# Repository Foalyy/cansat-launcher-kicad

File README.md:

Main electronics board (Kicad project) for the Argon CanSat launchers : https://github.com/Foalyy/cansat-launcher

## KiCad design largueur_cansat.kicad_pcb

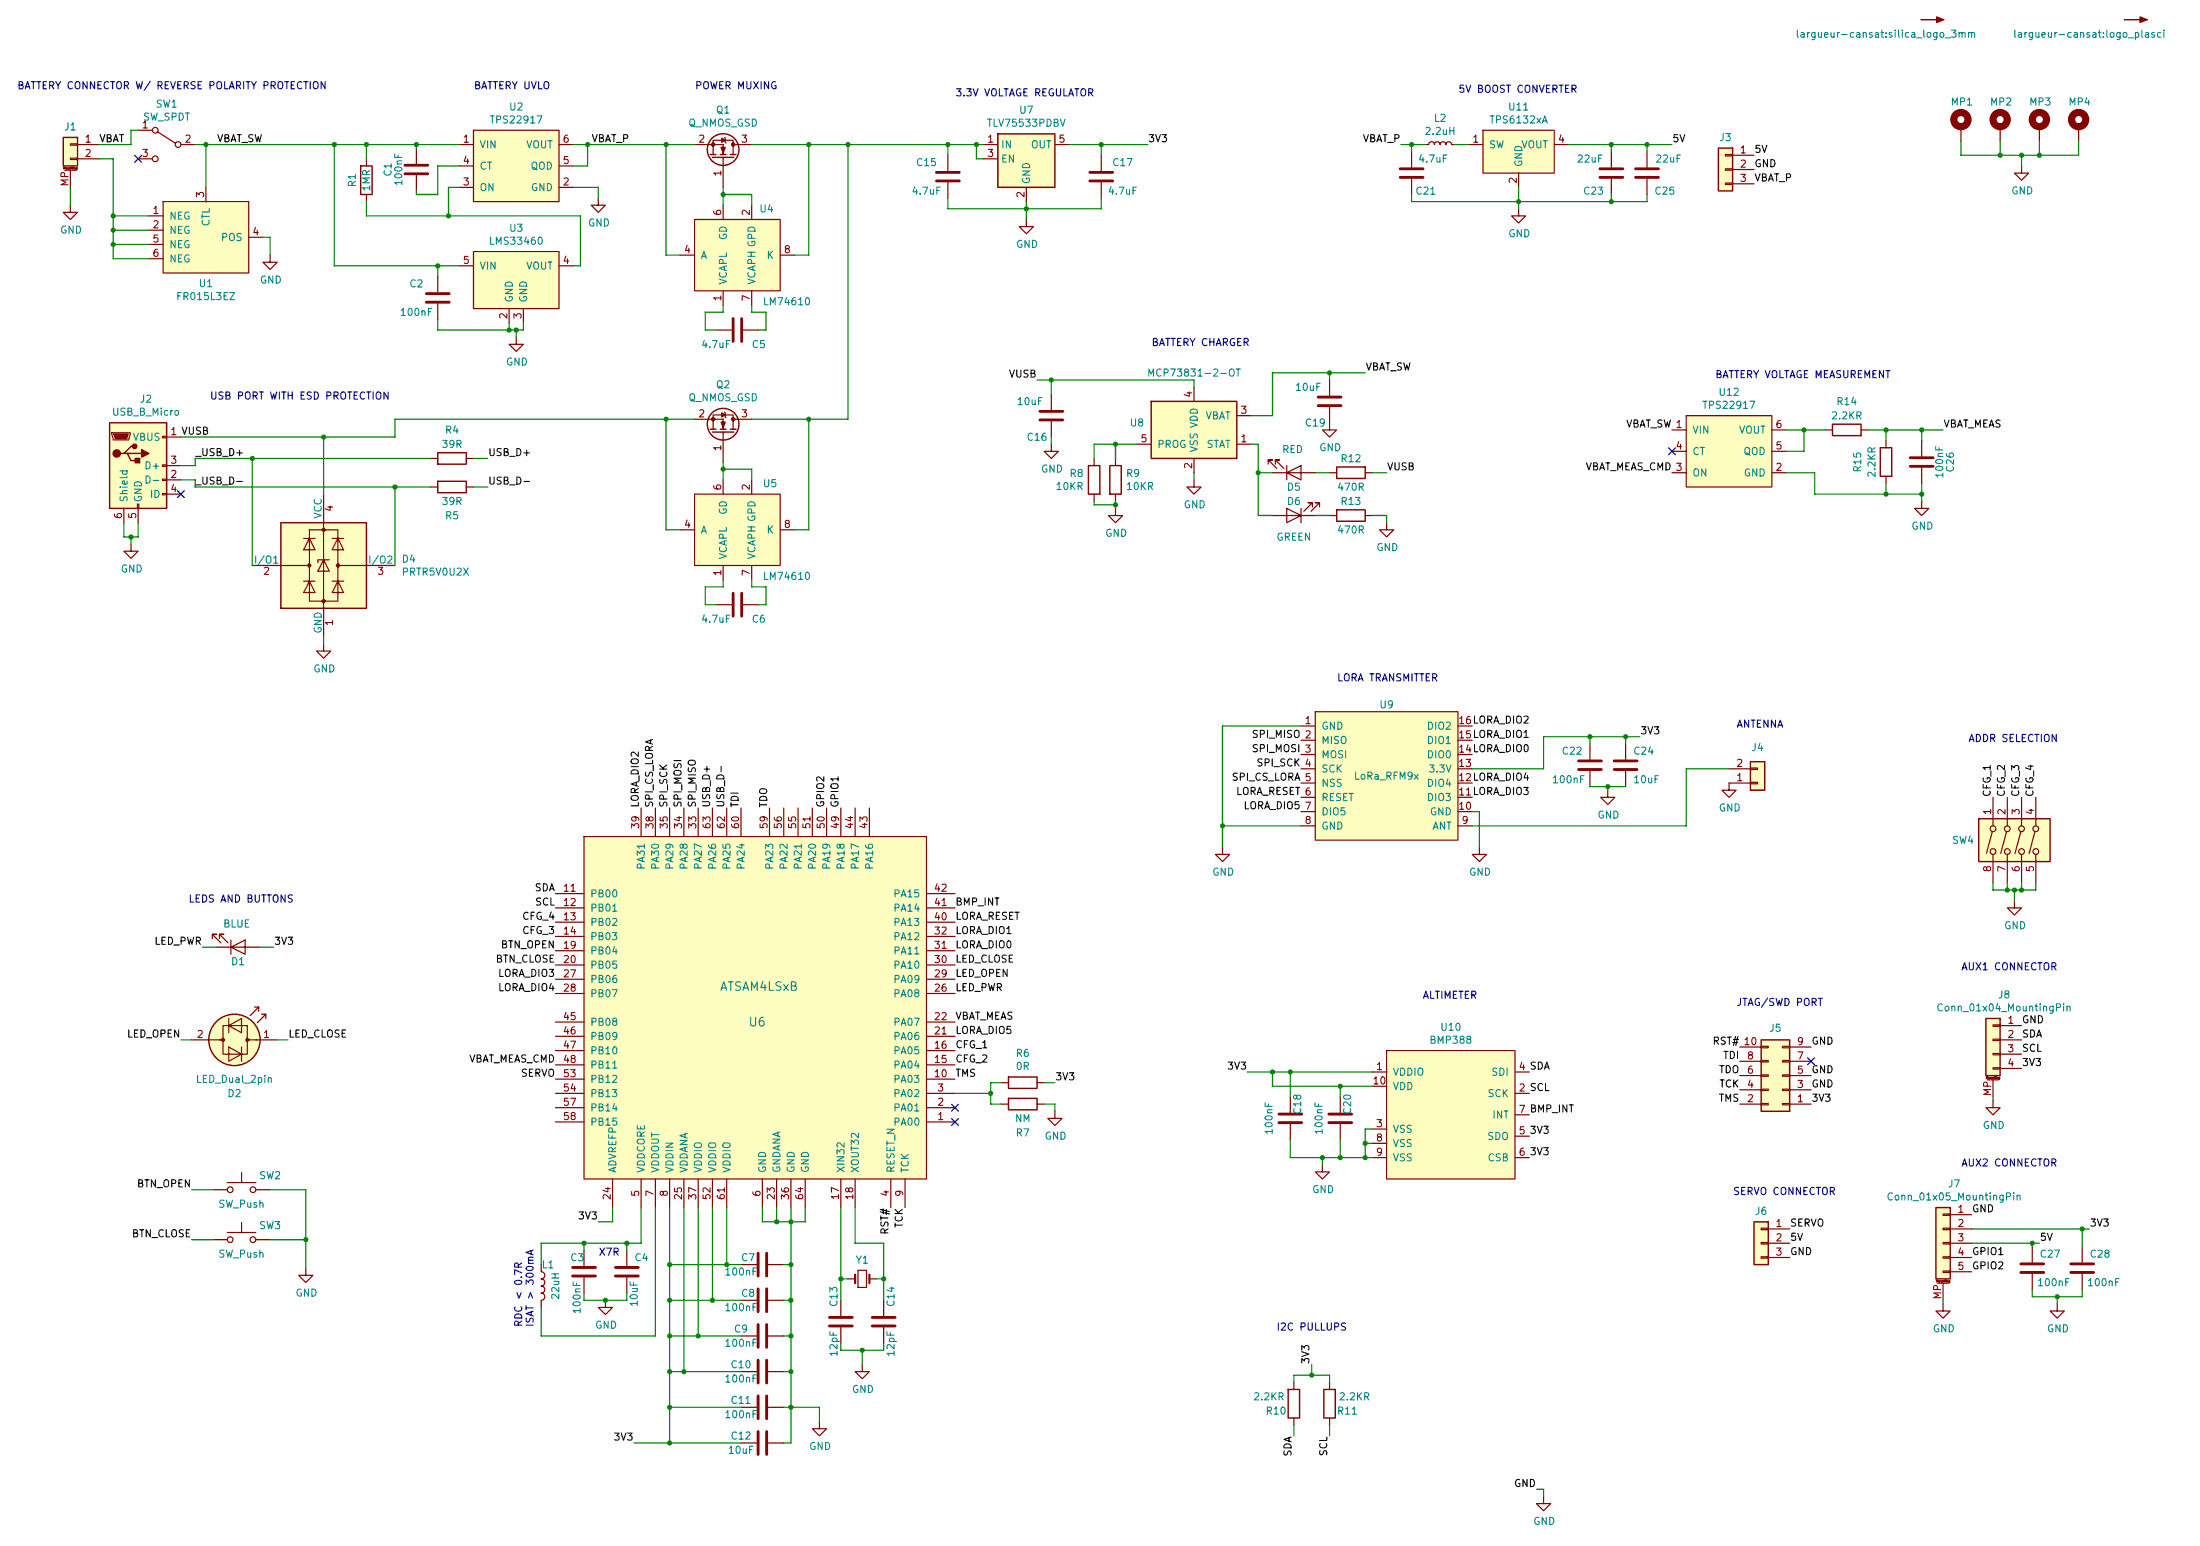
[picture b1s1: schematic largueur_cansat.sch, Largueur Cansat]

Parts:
C1, C2, C3, C7, C8, C9, C10, C11, C18, C20, C22, C26, C27, C28: 100nF; C_0603_1608Metric_Pad1.05x0.95mm_HandSolder; mpn 885012206071
C4, C12, C16, C19, C24: 10uF; C_0603_1608Metric_Pad1.05x0.95mm_HandSolder; mpn GRM188R61A106KE69J
C5, C6, C15, C17, C21: 4.7uF; C_0603_1608Metric_Pad1.05x0.95mm_HandSolder; mpn CC0603MRX5R6BB475
C13, C14: 12pF; C_0603_1608Metric_Pad1.05x0.95mm_HandSolder; mpn C0603C120K5RACTU
C23, C25: 22uF; C_0603_1608Metric_Pad1.05x0.95mm_HandSolder; mpn C1608X5R1A226M080AC
D1: BLUE; SSF-LXH103; mpn SSF-LXH103USBD
D2: LED_Dual_2pin; SSF-LXH103; mpn SSF-LXH103HGW
D4: PRTR5V0U2X; SOT-143; mpn PRTR5V0U2X
D5: RED; LED_Rectangular_W3.9mm_H1.9mm; mpn WP144SRDT
D6: GREEN; LED_Rectangular_W3.9mm_H1.9mm; mpn WP144GDT
J1: Conn_01x02_MountingPin; JST_SH_SM02B-SRSS-TB_1x02-1MP_P1.00mm_Horizontal
J2: USB_B_Micro; USB_Micro-B_Molex-105017-0001; mpn 105017-0001
J3: Conn_01x03; PinHeader_1x03_P2.54mm_Vertical
J4: Conn_01x02; antenna_sma_ufl
J5: Conn_02x05_Odd_Even; jtag_connector
J6: Conn_01x03; PinHeader_1x03_P2.54mm_Horizontal
J7: Conn_01x05_MountingPin; JST_SH_SM05B-SRSS-TB_1x05-1MP_P1.00mm_Horizontal
J8: Conn_01x04_MountingPin; JST_SH_SM04B-SRSS-TB_1x04-1MP_P1.00mm_Horizontal
L1: 22uH; L_1210_3225Metric_Pad1.42x2.65mm_HandSolder; mpn CBC3225T220MRV
L2: 2.2uH; L_0805_2012Metric; mpn TFM201610GHM-2R2MTAA
MP1, MP2, MP3, MP4: MountingHole_Pad; MountingHole_2.7mm_M2.5_Pad
Q1, Q2: Q_NMOS_GSD; SOT-23; mpn NTR3C21NZT1G
R1: 1MR; R_0603_1608Metric_Pad1.05x0.95mm_HandSolder
R4, R5: 39R; R_0603_1608Metric_Pad1.05x0.95mm_HandSolder; mpn RC0603FR-0739RL
R6: 0R; R_0603_1608Metric_Pad1.05x0.95mm_HandSolder; mpn AC0603JR-130RL
R7: NM; R_0603_1608Metric_Pad1.05x0.95mm_HandSolder
R8, R9: 10KR; R_0603_1608Metric_Pad1.05x0.95mm_HandSolder; mpn RC0603FR-0710KL
R10, R11, R14, R15: 2.2KR; R_0603_1608Metric_Pad1.05x0.95mm_HandSolder; mpn RC0603JR-072K2L
R12, R13: 470R; R_0603_1608Metric_Pad1.05x0.95mm_HandSolder; mpn RC0603FR-07470RL
SW1: SW_SPDT; SSSS213100; mpn SSSS213100
SW2: SW_Push; SW_Tactile_SPST_Angled_PTS645Vx83-2LFS; mpn 1-1825027-2
SW3: SW_Push; SW_Tactile_SPST_Angled_PTS645Vx83-2LFS; mpn FSMRA4JH04
SW4: SW_DIP_x04; TDA04H0SB1; mpn TDA04H0SB1
SYM1: SYM_Arrow_Small; logo_plasci
SYM2: SYM_Arrow_Small; silica_logo_3mm
U1: FR015L3EZ; mpn FR015L3EZ
U2: TPS22917; SOT-23-6; mpn TPS22917DBV
U3: LMS33460; SOT-353_SC-70-5; mpn LMS33460
U4, U5: LM74610; VSSOP-8_3.0x3.0mm_P0.65mm; mpn LM74610
U6: ATSAM4LSxB; LQFP-64_10x10mm_P0.5mm; mpn ATSAM4LS2BA-AU
U7: TLV75533PDBV; SOT-23-5; mpn TLV75533PDBVR
U8: MCP73831-2-OT; SOT-23-5; mpn MCP73831T-2ATI/OT
U9: LoRa_RFM9x; HOPERF_RFM9XW_SMD
U10: BMP388; mpn BMP388
U11: TPS6132xA; SOT-23-5; mpn TPS61322A
U12: TPS22917; SOT-23-6_Handsoldering; mpn TPS22917DBV
Y1: Crystal_Small; quartz_abs06; mpn ABS06-32.768KHZ-9-1-T

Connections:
/3V3: C7.2, C8.2, C9.2, C10.2, C11.2, C12.2, C17.1, C18.2, C20.2, C22.1, C24.1, C28.1, D1.2 (A), J5.1, J7.2, J8.4, R6.1, R10.2, R11.2, U6.8 (VDDIN), U6.24 (ADVREFP), U6.25 (VDDANA), U6.37 (VDDIO), U6.52 (VDDIO), U6.61 (VDDIO), U7.5 (OUT), U9.13 (3.3V), U10.1 (VDDIO), U10.5 (SDO), U10.6 (CSB), U10.10 (VDD)
/5V: C23.2, C25.2, C27.1, J3.1, J6.2, J7.3, U11.4 (VOUT)
/BMP_INT: U6.41 (PA14), U10.7 (INT)
/BTN_CLOSE: SW3.1, U6.20 (PB05)
/BTN_OPEN: SW2.1, U6.19 (PB04)
/CFG_1: SW4.1, U6.16 (PA05)
/CFG_2: SW4.2, U6.15 (PA04)
/CFG_3: SW4.3, U6.14 (PB03)
/CFG_4: SW4.4, U6.13 (PB02)
/GPIO1: J7.4, U6.49 (PA18)
/GPIO2: J7.5, U6.50 (PA19)
/LED_CLOSE: D2.1 (KA), U6.30 (PA10)
/LED_OPEN: D2.2 (AK), U6.29 (PA09)
/LED_PWR: D1.1 (K), U6.26 (PA08)
/LORA_DIO0: U6.31 (PA11), U9.14 (DIO0)
/LORA_DIO1: U6.32 (PA12), U9.15 (DIO1)
/LORA_DIO2: U6.39 (PA31), U9.16 (DIO2)
/LORA_DIO3: U6.27 (PB06), U9.11 (DIO3)
/LORA_DIO4: U6.28 (PB07), U9.12 (DIO4)
/LORA_DIO5: U6.21 (PA06), U9.7 (DIO5)
/LORA_RESET: U6.40 (PA13), U9.6 (RESET)
/RST#: J5.10, U6.4 (RESET_N)
/SCL: J8.3, R11.1, U6.12 (PB01), U10.2 (SCK)
/SDA: J8.2, R10.1, U6.11 (PB00), U10.4 (SDI)
/SERVO: J6.1, U6.53 (PB12)
/SPI_CS_LORA: U6.38 (PA30), U9.5 (NSS)
/SPI_MISO: U6.33 (PA27), U9.2 (MISO)
/SPI_MOSI: U6.34 (PA28), U9.3 (MOSI)
/SPI_SCK: U6.35 (PA29), U9.4 (SCK)
/TCK: J5.4, U6.9 (TCK)
/TDI: J5.8, U6.60 (PA24)
/TDO: J5.6, U6.59 (PA23)
/TMS: J5.2, U6.10 (PA03)
/USB_D+: R4.1, U6.63 (PA26)
/USB_D-: R5.1, U6.62 (PA25)
/VBAT: J1.1, SW1.1 (A)
/VBAT_MEAS: C26.2, R14.2, R15.1, U6.22 (PA07)
/VBAT_MEAS_CMD: U6.48 (PB11), U12.3 (ON)
/VBAT_P: C21.2, J3.3, L2.1, Q1.2 (S), U2.5 (QOD), U2.6 (VOUT), U4.4 (A)
/VBAT_SW: C1.1, C2.1, C19.2, R1.2, SW1.2 (B), U1.3 (CTL), U2.1 (VIN), U3.5 (VIN), U8.3 (VBAT), U12.1 (VIN)
/VUSB: C16.2, D4.4 (VCC), J2.1 (VBUS), Q2.2 (S), R12.2, U5.4 (A), U8.4 (VDD)
/_USB_D+: D4.2 (I/O1), J2.3 (D+), R4.2
/_USB_D-: D4.3 (I/O2), J2.2 (D-), R5.2
GND: C2.2, C3.2, C4.2, C7.1, C8.1, C9.1, C10.1, C11.1, C12.1, C13.2, C14.2, C15.2, C16.1, C17.2, C18.1, C19.1, C20.1, C21.1, C22.2, C23.1, C24.2, C25.1, C26.1, C27.2, C28.2, D4.1 (GND), J1.MP (MountPin), J2.5 (GND), J2.6 (Shield), J3.2, J4.1, J5.3, J5.5, J5.9, J6.3, J7.1, J7.MP (MountPin), J8.1, J8.MP (MountPin), MP1.1, MP2.1, MP3.1, MP4.1, R7.1, R8.2, R9.2, R13.1, R15.2, SW2.2, SW3.2, SW4.5, SW4.6, SW4.7, SW4.8, U1.4 (POS), U2.2 (GND), U3.2 (GND), U3.3 (GND), U6.6 (GND), U6.23 (GNDANA), U6.36 (GND), U6.64 (GND), U7.2 (GND), U8.2 (VSS), U9.1 (GND), U9.8 (GND), U9.10 (GND), U10.3 (VSS), U10.8 (VSS), U10.9 (VSS), U11.2 (GND), U12.2 (GND)
unnamed: C1.2, U2.4 (CT)
unnamed: C3.1, C4.1, L1.1, U6.5 (VDDCORE)
unnamed: C5.1, U4.1 (VCAPL)
unnamed: C5.2, U4.7 (VCAPH)
unnamed: C6.1, U5.1 (VCAPL)
unnamed: C6.2, U5.7 (VCAPH)
unnamed: C13.1, U6.17 (XIN32), Y1.1
unnamed: C14.1, U6.18 (XOUT32), Y1.2
unnamed: C15.1, Q1.3 (D), Q2.3 (D), U4.8 (K), U5.8 (K), U7.1 (IN), U7.3 (EN)
unnamed: D5.1 (K), D6.2 (A), U8.1 (STAT)
unnamed: D5.2 (A), R12.1
unnamed: D6.1 (K), R13.2
unnamed: J1.2, U1.1 (NEG), U1.2 (NEG), U1.5 (NEG), U1.6 (NEG)
unnamed: J4.2, U9.9 (ANT)
unnamed: L1.2, U6.7 (VDDOUT)
unnamed: L2.2, U11.1 (SW)
unnamed: Q1.1 (G), U4.2 (GPD), U4.6 (GD)
unnamed: Q2.1 (G), U5.2 (GPD), U5.6 (GD)
unnamed: R1.1, U2.3 (ON), U3.4 (VOUT)
unnamed: R6.2, R7.2, U6.3 (PA02)
unnamed: R8.1, R9.1, U8.5 (PROG)
unnamed: R14.1, U12.5 (QOD), U12.6 (VOUT)

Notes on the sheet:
RDC < 0.7R ISAT > 300mA
X7R
ANTENNA
USB PORT WITH ESD PROTECTION
BATTERY CONNECTOR W/ REVERSE POLARITY PROTECTION
BATTERY CHARGER
LORA TRANSMITTER
JTAG/SWD PORT
BATTERY VOLTAGE MEASUREMENT
LEDS AND BUTTONS
BATTERY UVLO
3.3V VOLTAGE REGULATOR
SERVO CONNECTOR
ADDR SELECTION
AUX1 CONNECTOR
ALTIMETER
I2C PULLUPS
5V BOOST CONVERTER
POWER MUXING
AUX2 CONNECTOR

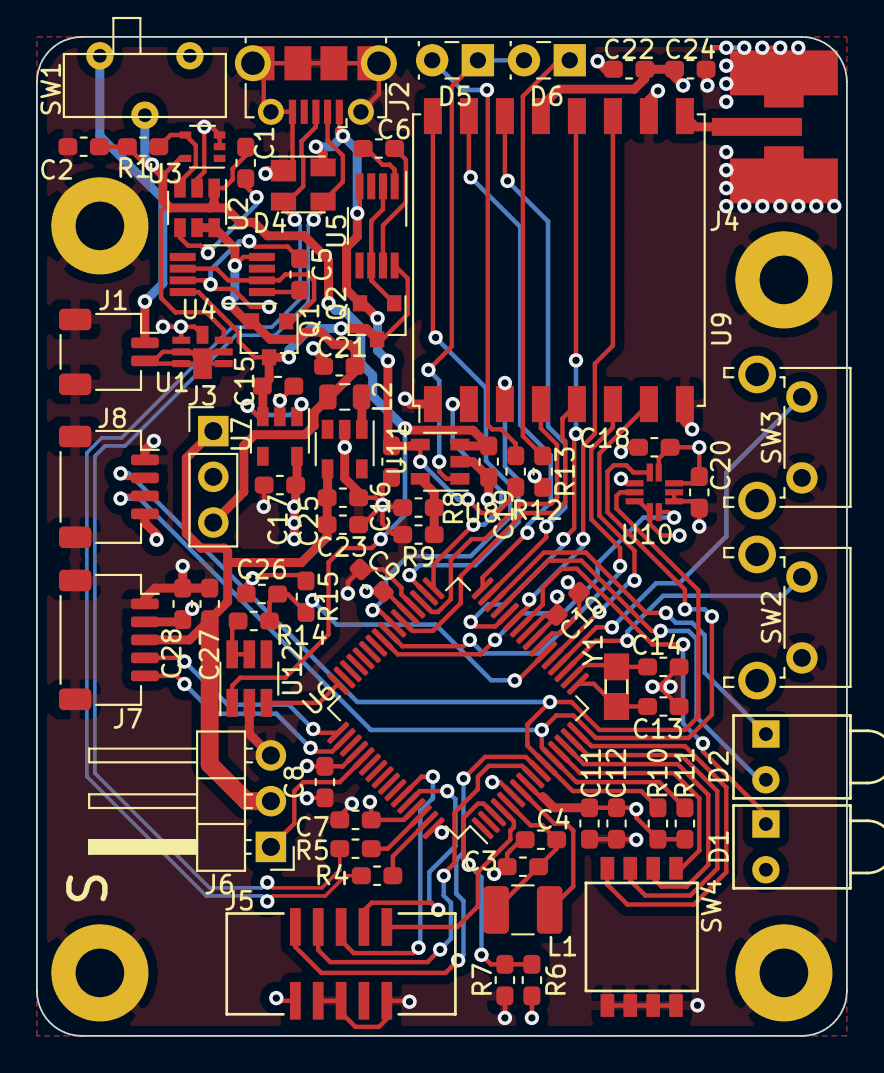
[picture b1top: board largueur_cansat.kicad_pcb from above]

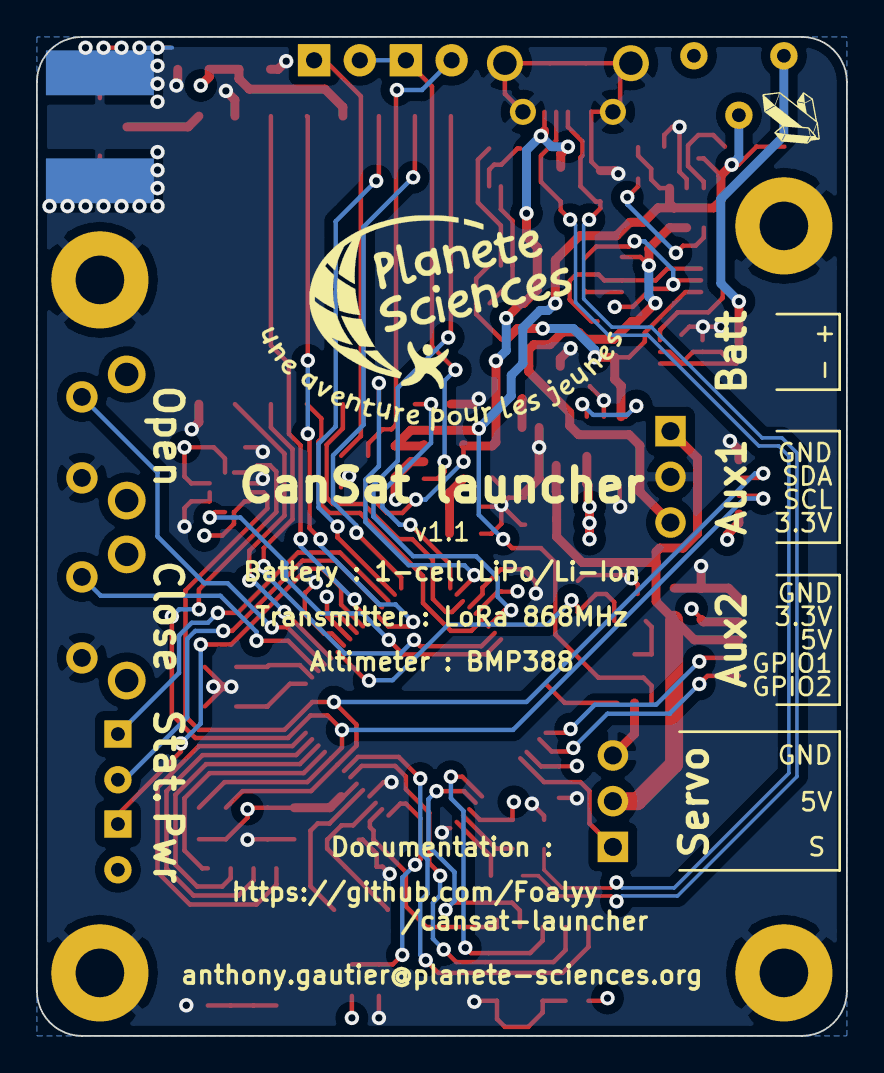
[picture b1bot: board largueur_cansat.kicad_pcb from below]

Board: 4 copper layers, 45.0 x 55.5 mm, 81 parts (2 on the bottom side), 66 nets.

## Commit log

2019-07-03 v1.1
2019-08-11 Added README
